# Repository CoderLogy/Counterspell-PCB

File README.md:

# Counterspell-PCB
✨ Features

    Ultra compact keychain design

    Smooth fading LED effect

    Low power usage – runs on a coin cell!

    Simple circuitry with only a handful of components

    Counterspell logo on the front – mysterious and magical

## Schema

## PCB Front

## PCB Back

🔧 How to build

Just order the PCB & components, open the KiCAD file, and solder it up! Perfect for a quick weekend project or a beginner's intro to electronics.

📦 BOM (Bill of Materials)

    1× Push Button

    1× Battery Holder

    1× 10µF Capacitor

    3× 220Ω Resistors

    3× LEDs

Made as a part of http://solder.hackclub.com/

Thanks a lot https://www.pcbway.com/ for supporting this project !

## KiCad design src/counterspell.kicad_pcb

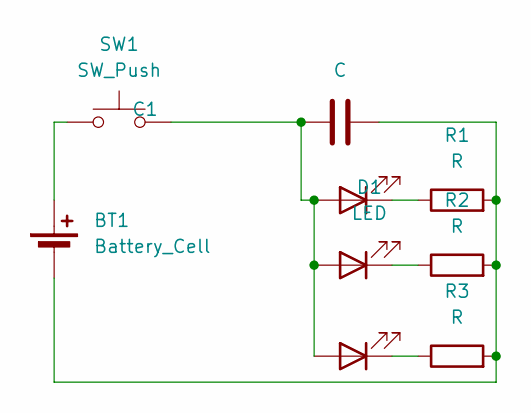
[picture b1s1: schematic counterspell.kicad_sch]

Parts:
BT1: Battery_Cell; BatteryHolder_Keystone_3034_1x20mm
C1: C; CP_Radial_D8.0mm_P5.00mm
D1, D2, D3: LED; LED_D5.0mm
R1, R2, R3: R; R_Axial_DIN0207_L6.3mm_D2.5mm_P7.62mm_Horizontal
SW1: SW_Push; SW_PUSH_6mm

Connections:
unnamed: BT1.1 (+), SW1.1
unnamed: BT1.2 (-), C1.2, R1.2, R2.2, R3.2
unnamed: C1.1, D1.2 (A), D2.2 (A), D3.2 (A), SW1.2
unnamed: D1.1 (K), R2.1
unnamed: D2.1 (K), R3.1
unnamed: D3.1 (K), R1.1

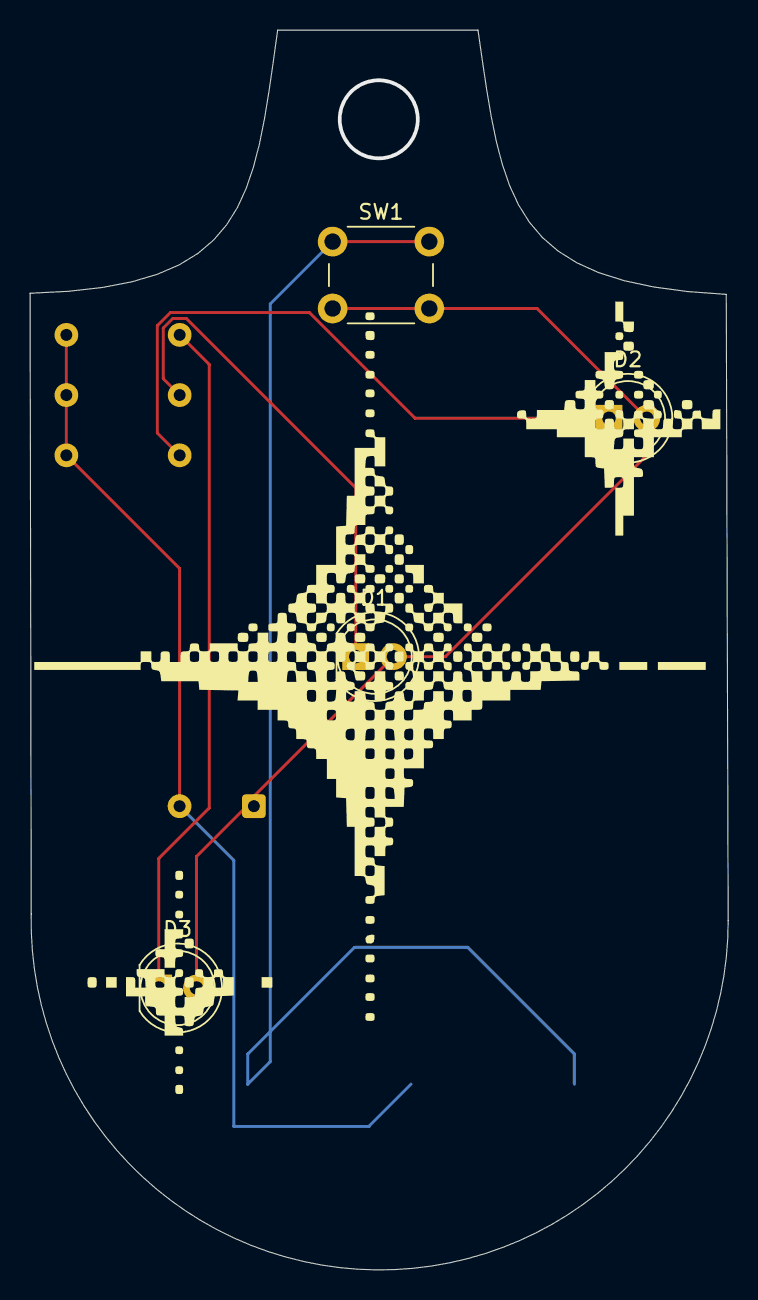
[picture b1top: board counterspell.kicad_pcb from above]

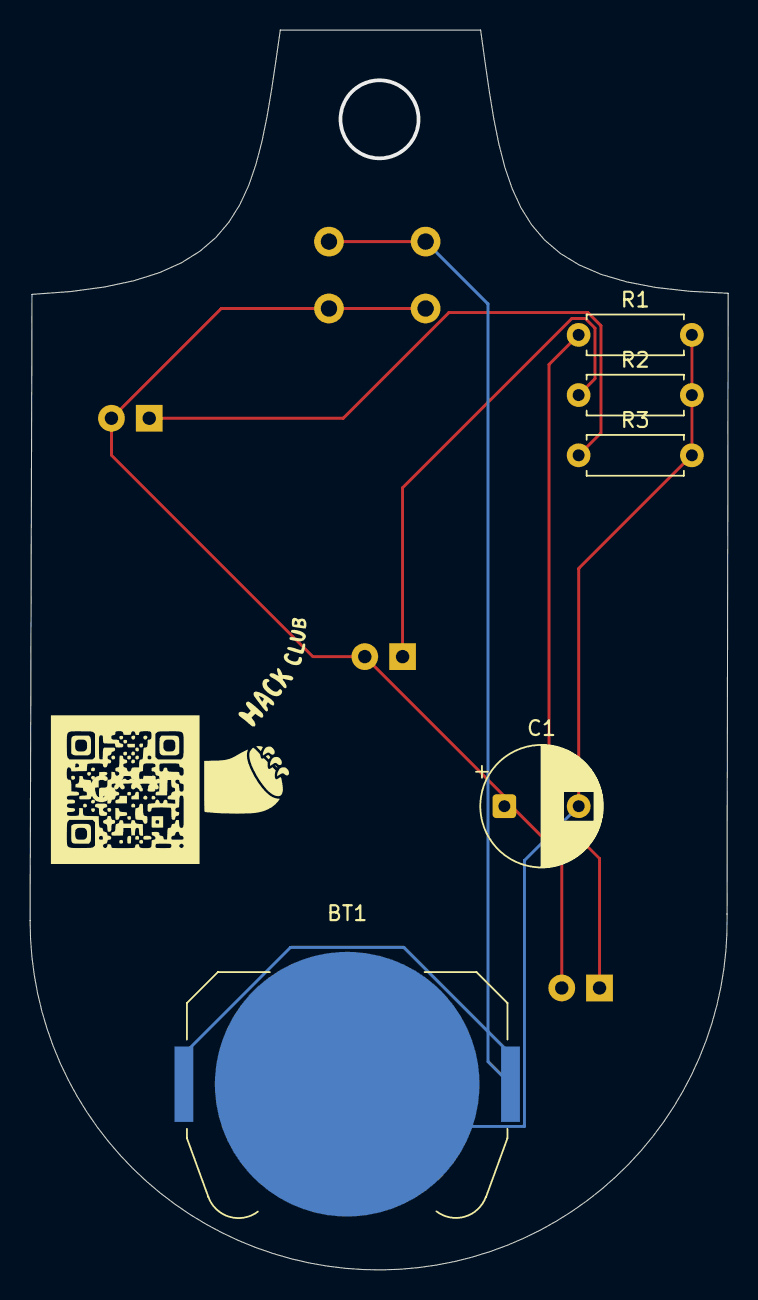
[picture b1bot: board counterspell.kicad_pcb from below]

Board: 2 copper layers, 47.0 x 83.4 mm, 9 parts (5 on the bottom side), 6 nets.

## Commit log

2025-05-20 important stuff
2025-05-22 perfect changed the whole board outlook like resized it
2025-05-22 fixed stuff
2025-05-24 important
